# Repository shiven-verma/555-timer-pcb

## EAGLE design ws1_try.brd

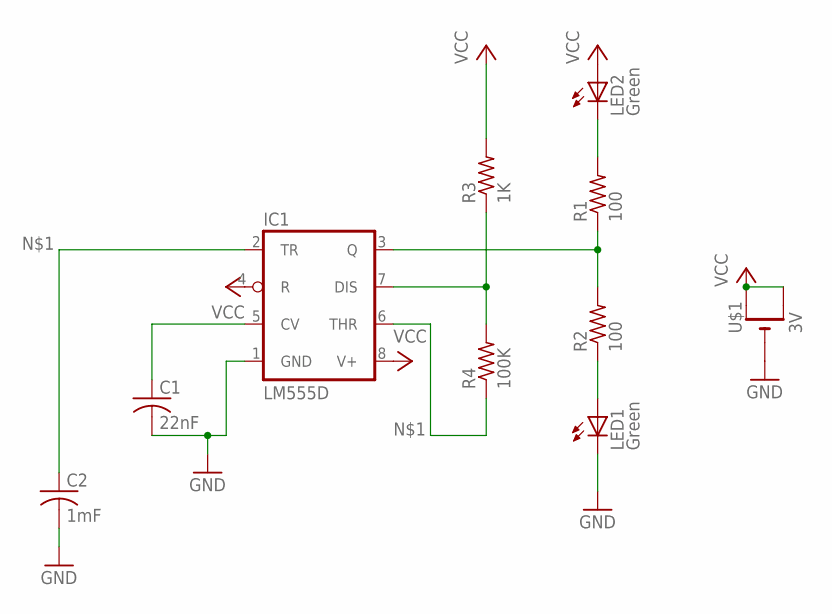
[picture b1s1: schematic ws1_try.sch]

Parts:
C1: 22nF; C0805
C2: 1mF; C0805
IC1: LM555D; SO08
LED1, LED2: Green; CHIP-LED0805
R1, R2: 100; R0805
R3: 1K; R0805
R4: 100K; R0805
U$1: 3V; CR1220-SMD

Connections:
GND: C1.2, C2.2, IC1.1 (GND), LED1.C, U$1.-
unnamed: C2.1, IC1.2 (TR), IC1.6 (THR), R4.1
unnamed: C1.1, IC1.5 (CV)
unnamed: LED2.C, R1.2
unnamed: IC1.3 (Q), R1.1, R2.2
unnamed: LED1.A, R2.1
unnamed: IC1.7 (DIS), R3.1, R4.2
VCC: IC1.4 (R), IC1.8 (V+), LED2.A, R3.2, U$1.+$1 (+), U$1.+$2 (+1)

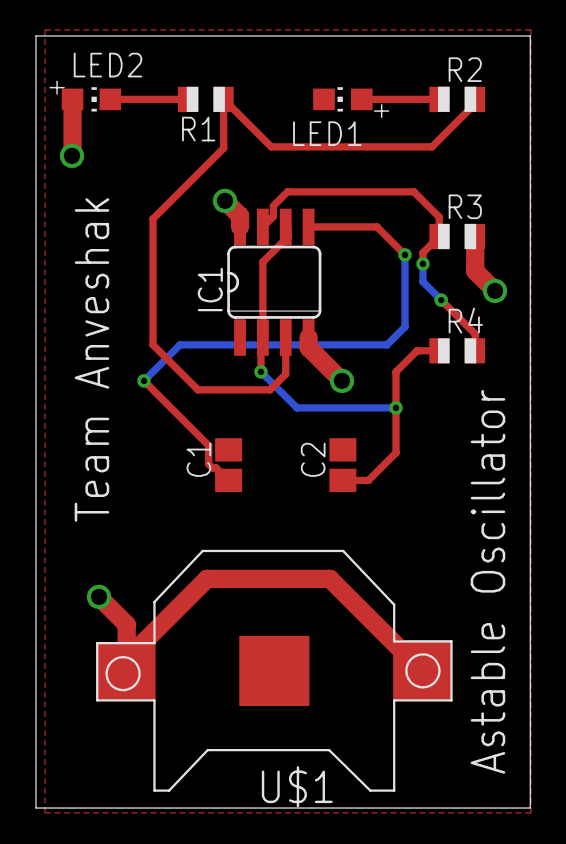
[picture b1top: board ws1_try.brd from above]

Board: 2 copper layers, 27.5 x 42.9 mm, 10 parts (0 on the bottom side), 8 nets.
